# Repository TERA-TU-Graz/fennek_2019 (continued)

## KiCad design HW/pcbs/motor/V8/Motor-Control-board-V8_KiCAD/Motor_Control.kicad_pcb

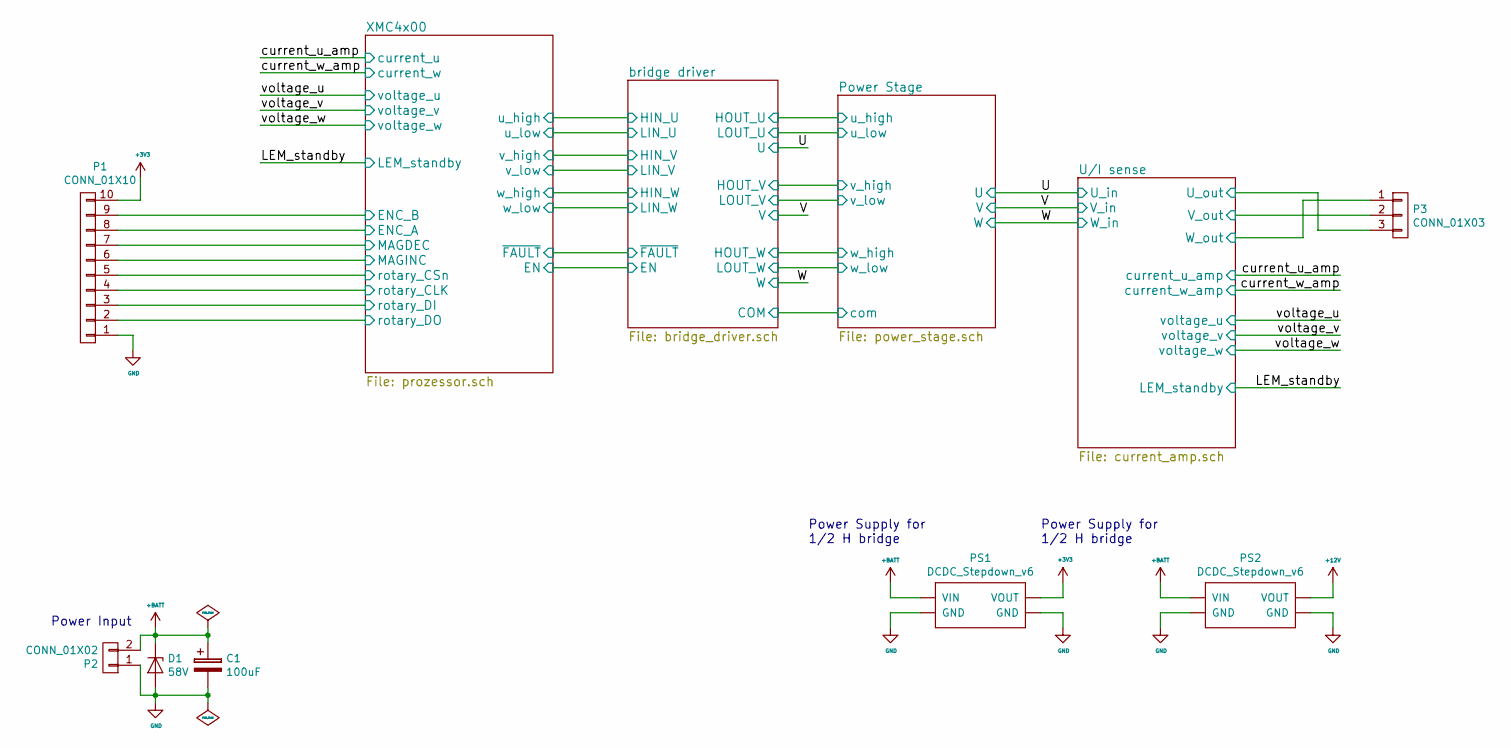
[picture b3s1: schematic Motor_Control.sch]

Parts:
C1: 100uF; ElkoC-12.5x20mm-horizontal
D1: 58V; DO-214AA
P1: CONN_01X10; Molex_PicoBlade_53261-1071_10x1.25mm_Angled
P2: CONN_01X02; MSTBV_2.5_2-GF-5.08mm
P3: CONN_01X03; PhoenixContact_MSTBA-G_03x5.08mm_Angled
PS1, PS2: DCDC_Stepdown_v6

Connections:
+3V3: P1.10, PS1.2 (VOUT); also elsewhere on the board
+12V: PS2.2 (VOUT); also elsewhere on the board
+BATT: C1.1, D1.1 (K), P2.2, PS1.1 (VIN), PS2.1 (VIN); also elsewhere on the board
/U/I sense/U_out: P3.3; also elsewhere on the board
/U/I sense/W_out: P3.1; also elsewhere on the board
/V: P3.2; also elsewhere on the board
/XMC4x00/ENC_A: P1.8; also elsewhere on the board
/XMC4x00/ENC_B: P1.9; also elsewhere on the board
/XMC4x00/MAGDEC: P1.7; also elsewhere on the board
/XMC4x00/MAGINC: P1.6; also elsewhere on the board
/XMC4x00/rotary_CLK: P1.4; also elsewhere on the board
/XMC4x00/rotary_CSn: P1.5; also elsewhere on the board
/XMC4x00/rotary_DI: P1.3; also elsewhere on the board
/XMC4x00/rotary_DO: P1.2; also elsewhere on the board
GND: C1.2, D1.2 (A), P1.1, P2.1, PS1.3 (GND), PS1.4 (GND), PS2.3 (GND), PS2.4 (GND); also elsewhere on the board

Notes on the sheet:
Power Supply for 1/2 H bridge
Power Input

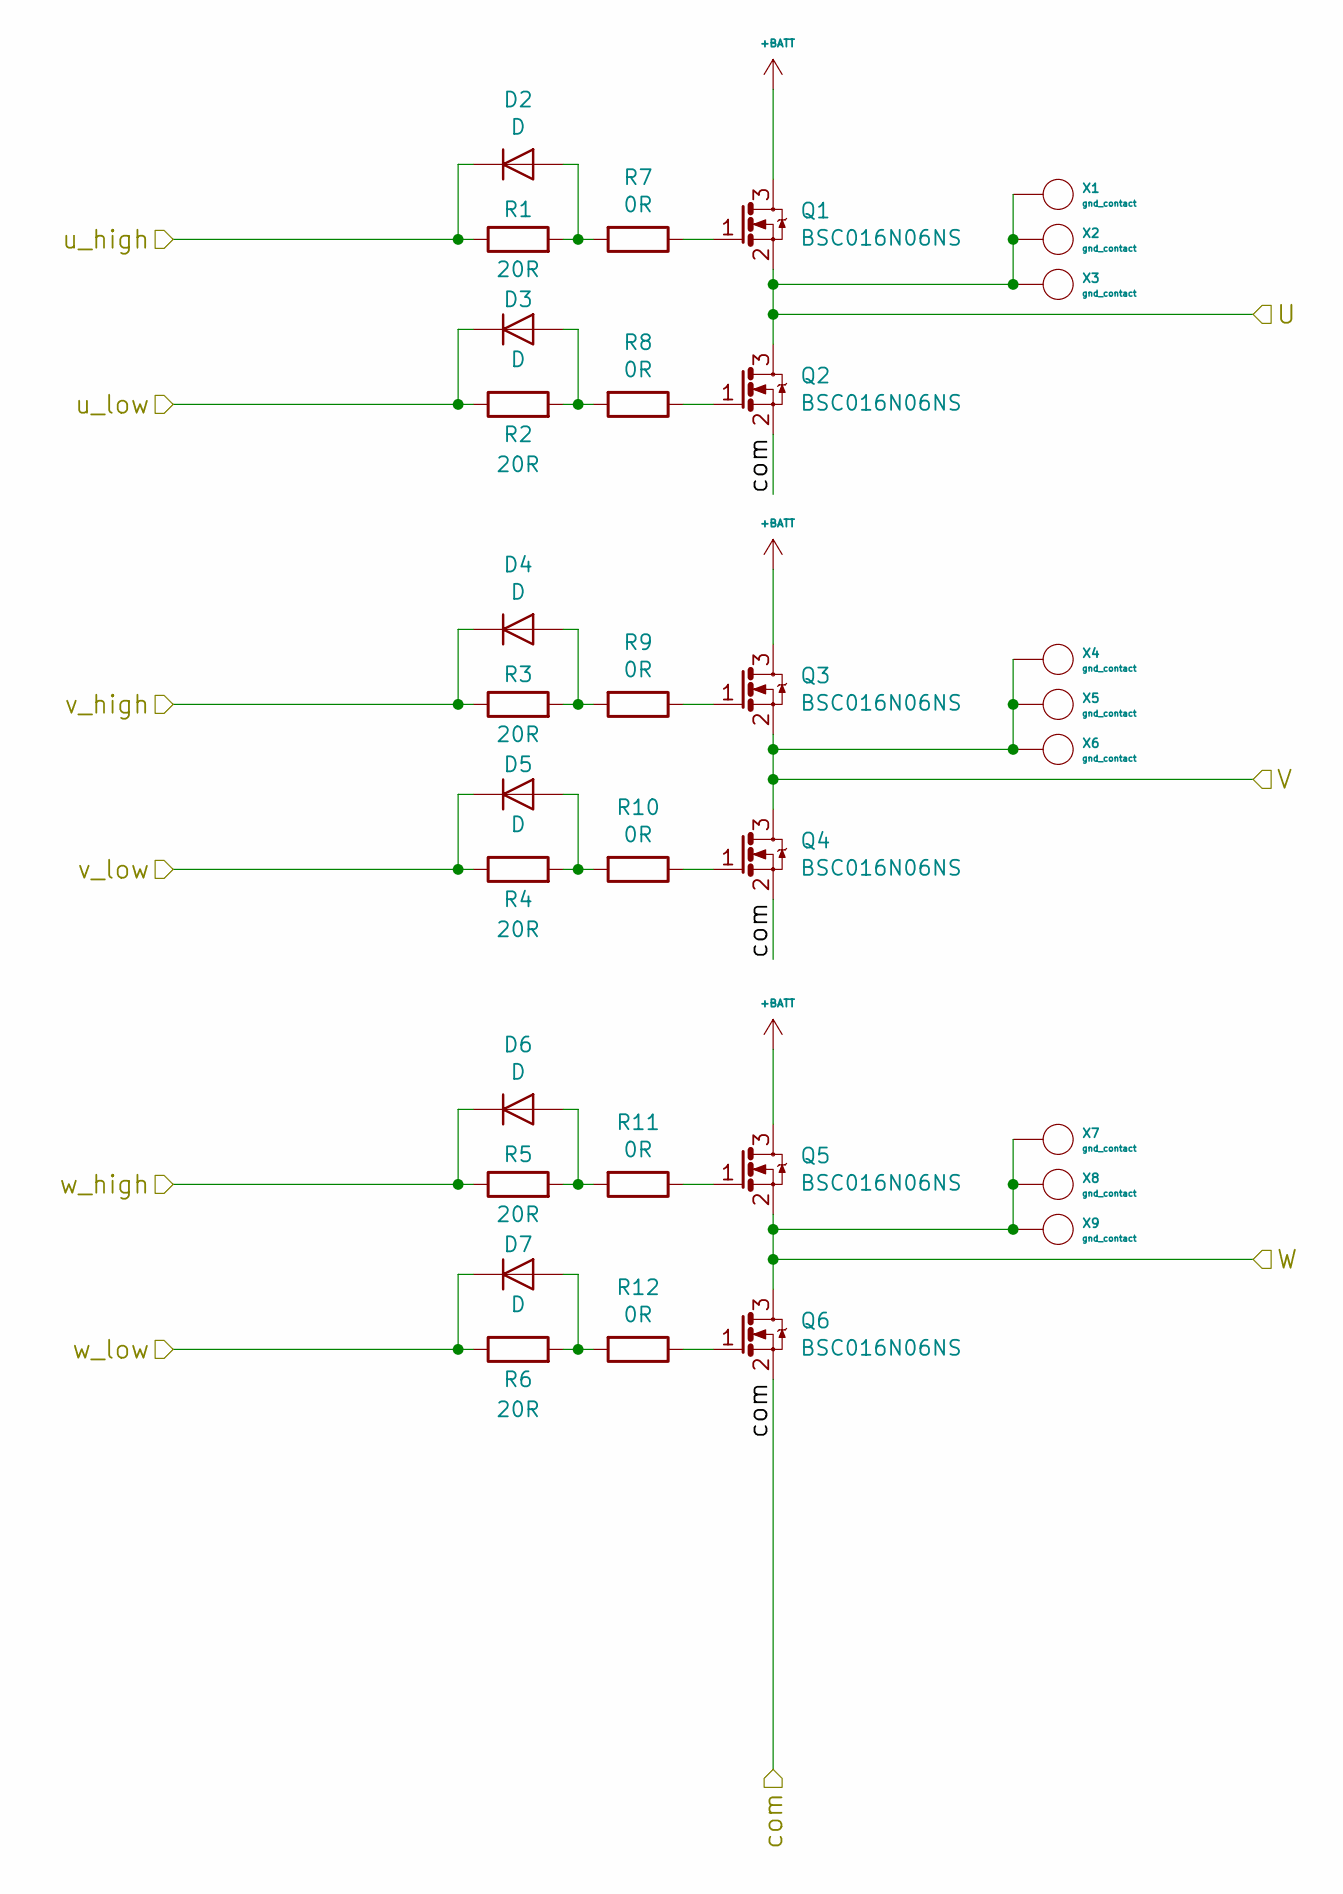
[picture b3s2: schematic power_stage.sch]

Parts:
D2, D3, D4, D5, D6, D7: D; SOD-323
Q1, Q2, Q3, Q4, Q5, Q6: BSC016N06NS; INF-PG-TDSON-8
R1, R2, R3, R4, R5, R6: 20R; R_0603in
R7, R8, R9, R10, R11, R12: 0R; R_0603in
X1, X2, X3, X4, X5, X6, X7, X8, X9: gnd_contact; via_0.4mm

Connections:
+BATT: Q1.3 (D), Q3.3 (D), Q5.3 (D); also elsewhere on the board
/U: Q1.2 (S), Q2.3 (D), X1.1, X2.1, X3.1; also elsewhere on the board
/V: Q3.2 (S), Q4.3 (D), X4.1, X5.1, X6.1; also elsewhere on the board
/W: Q5.2 (S), Q6.3 (D), X7.1, X8.1, X9.1; also elsewhere on the board
/bridge driver/COM: Q2.2 (S), Q4.2 (S), Q6.2 (S); also elsewhere on the board
/bridge driver/HOUT_U: D2.1 (K), R1.1; also elsewhere on the board
/bridge driver/HOUT_V: D4.1 (K), R3.1; also elsewhere on the board
/bridge driver/HOUT_W: D6.1 (K), R5.1; also elsewhere on the board
/bridge driver/LOUT_U: D3.1 (K), R2.1; also elsewhere on the board
/bridge driver/LOUT_V: D5.1 (K), R4.1; also elsewhere on the board
/bridge driver/LOUT_W: D7.1 (K), R6.1; also elsewhere on the board
unnamed: D2.2 (A), R1.2, R7.2
unnamed: D3.2 (A), R2.2, R8.2
unnamed: D4.2 (A), R3.2, R9.2
unnamed: D5.2 (A), R4.2, R10.2
unnamed: D6.2 (A), R5.2, R11.2
unnamed: D7.2 (A), R6.2, R12.2
unnamed: Q1.1 (G), R7.1
unnamed: Q2.1 (G), R8.1
unnamed: Q3.1 (G), R9.1
unnamed: Q4.1 (G), R10.1
unnamed: Q5.1 (G), R11.1
unnamed: Q6.1 (G), R12.1

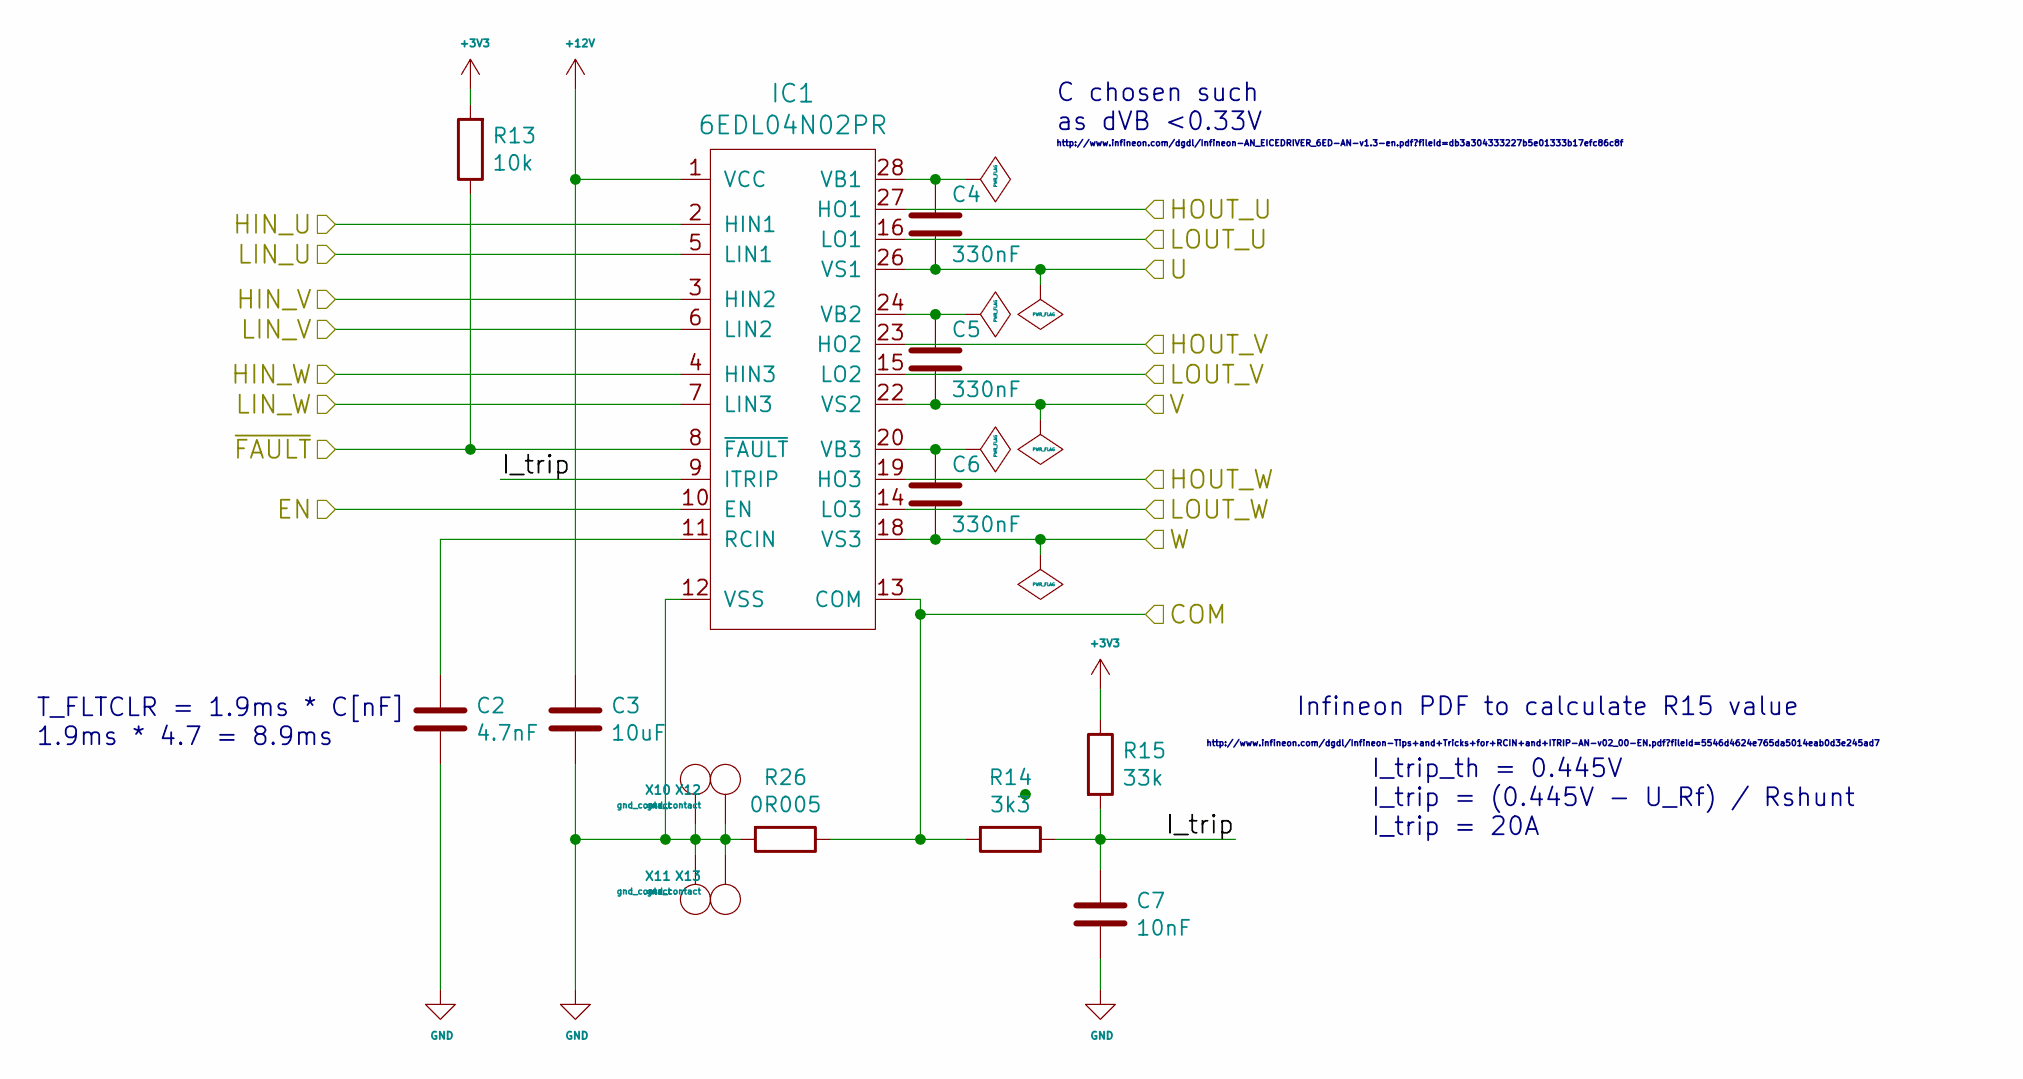
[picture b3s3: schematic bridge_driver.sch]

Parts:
C2: 4.7nF; C_0603in
C3: 10uF; C_0603in
C4, C5, C6: 330nF; C_0603in
C7: 10nF; C_0603in
IC1: 6EDL04N02PR
R13: 10k; R_0603in
R14: 3k3; R_0603in
R15: 33k; R_0603in
R26: 0R005; R_2512in
X10, X11, X12, X13: gnd_contact; via_0.4mm

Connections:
+3V3: R13.2, R15.1; also elsewhere on the board
+12V: C3.1, IC1.1 (VCC); also elsewhere on the board
/U: C4.2, IC1.26 (VS1); also elsewhere on the board
/V: C5.2, IC1.22 (VS2); also elsewhere on the board
/W: C6.2, IC1.18 (VS3); also elsewhere on the board
/XMC4x00/EN: IC1.10 (EN); also elsewhere on the board
/XMC4x00/~FAULT: IC1.8 (~FAULT), R13.1; also elsewhere on the board
/bridge driver/COM: IC1.13 (COM), R14.2, R26.1; also elsewhere on the board
/bridge driver/HIN_U: IC1.2 (HIN1); also elsewhere on the board
/bridge driver/HIN_V: IC1.3 (HIN2); also elsewhere on the board
/bridge driver/HIN_W: IC1.4 (HIN3); also elsewhere on the board
/bridge driver/HOUT_U: IC1.27 (HO1); also elsewhere on the board
/bridge driver/HOUT_V: IC1.23 (HO2); also elsewhere on the board
/bridge driver/HOUT_W: IC1.19 (HO3); also elsewhere on the board
/bridge driver/I_trip: C7.1, IC1.9 (ITRIP), R14.1, R15.2
/bridge driver/LIN_U: IC1.5 (LIN1); also elsewhere on the board
/bridge driver/LIN_V: IC1.6 (LIN2); also elsewhere on the board
/bridge driver/LIN_W: IC1.7 (LIN3); also elsewhere on the board
/bridge driver/LOUT_U: IC1.16 (LO1); also elsewhere on the board
/bridge driver/LOUT_V: IC1.15 (LO2); also elsewhere on the board
/bridge driver/LOUT_W: IC1.14 (LO3); also elsewhere on the board
GND: C2.2, C3.2, C7.2, IC1.12 (VSS), R26.2, X10.1, X11.1, X12.1, X13.1; also elsewhere on the board
unnamed: C2.1, IC1.11 (RCIN)
unnamed: C4.1, IC1.28 (VB1)
unnamed: C5.1, IC1.24 (VB2)
unnamed: C6.1, IC1.20 (VB3)

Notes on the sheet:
http://www.infineon.com/dgdl/Infineon-Tips+and+Tricks+for+RCIN+and+ITRIP-AN-v02_00-EN.pdf?fileId=5546d4624e765da5014eab0d3e245ad7
Infineon PDF to calculate R15 value
T_FLTCLR = 1.9ms * C[nF] 1.9ms * 4.7 = 8.9ms
C chosen such as dVB <0.33V
I_trip_th = 0.445V I_trip = (0.445V - U_Rf) / Rshunt I_trip = 20A
http://www.infineon.com/dgdl/Infineon-AN_EICEDRIVER_6ED-AN-v1.3-en.pdf?fileId=db3a304333227b5e01333b17efc86c8f

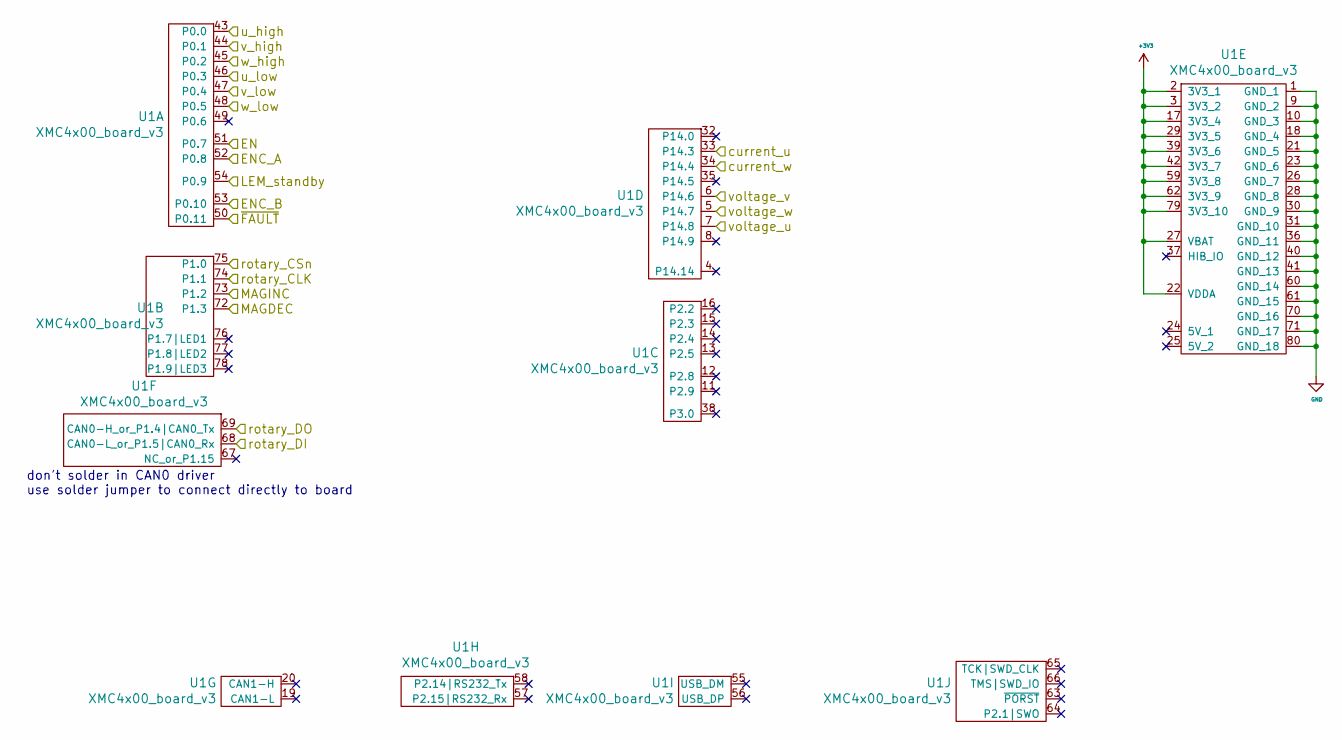
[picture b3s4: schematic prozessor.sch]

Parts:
U1: XMC4x00_board_v3; XMC4x00-board_v3-0

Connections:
+3V3: U1.2 (3V3_1), U1.3 (3V3_2), U1.17 (3V3_4), U1.22 (VDDA), U1.27 (VBAT), U1.29 (3V3_5), U1.39 (3V3_6), U1.42 (3V3_7), U1.59 (3V3_8), U1.62 (3V3_9), U1.79 (3V3_10); also elsewhere on the board
/LEM_standby: U1.54 (P0.9); also elsewhere on the board
/XMC4x00/EN: U1.51 (P0.7); also elsewhere on the board
/XMC4x00/ENC_A: U1.52 (P0.8); also elsewhere on the board
/XMC4x00/ENC_B: U1.53 (P0.10); also elsewhere on the board
/XMC4x00/MAGDEC: U1.72 (P1.3); also elsewhere on the board
/XMC4x00/MAGINC: U1.73 (P1.2); also elsewhere on the board
/XMC4x00/rotary_CLK: U1.74 (P1.1); also elsewhere on the board
/XMC4x00/rotary_CSn: U1.75 (P1.0); also elsewhere on the board
/XMC4x00/rotary_DI: U1.68 (CAN0-L_or_P1.5|CAN0_Rx); also elsewhere on the board
/XMC4x00/rotary_DO: U1.69 (CAN0-H_or_P1.4|CAN0_Tx); also elsewhere on the board
/XMC4x00/~FAULT: U1.50 (P0.11); also elsewhere on the board
/bridge driver/HIN_U: U1.43 (P0.0); also elsewhere on the board
/bridge driver/HIN_V: U1.44 (P0.1); also elsewhere on the board
/bridge driver/HIN_W: U1.45 (P0.2); also elsewhere on the board
/bridge driver/LIN_U: U1.46 (P0.3); also elsewhere on the board
/bridge driver/LIN_V: U1.47 (P0.4); also elsewhere on the board
/bridge driver/LIN_W: U1.48 (P0.5); also elsewhere on the board
/current_u_amp: U1.33 (P14.3); also elsewhere on the board
/current_w_amp: U1.34 (P14.4); also elsewhere on the board
/voltage_u: U1.7 (P14.8); also elsewhere on the board
/voltage_v: U1.6 (P14.6); also elsewhere on the board
/voltage_w: U1.5 (P14.7); also elsewhere on the board
GND: U1.1 (GND_1), U1.9 (GND_2), U1.10 (GND_3), U1.18 (GND_4), U1.21 (GND_5), U1.23 (GND_6), U1.26 (GND_7), U1.28 (GND_8), U1.30 (GND_9), U1.31 (GND_10), U1.36 (GND_11), U1.40 (GND_12), U1.41 (GND_13), U1.60 (GND_14), U1.61 (GND_15), U1.70 (GND_16), U1.71 (GND_17), U1.80 (GND_18); also elsewhere on the board

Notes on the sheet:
don't solder in CAN0 driver use solder jumper to connect directly to board

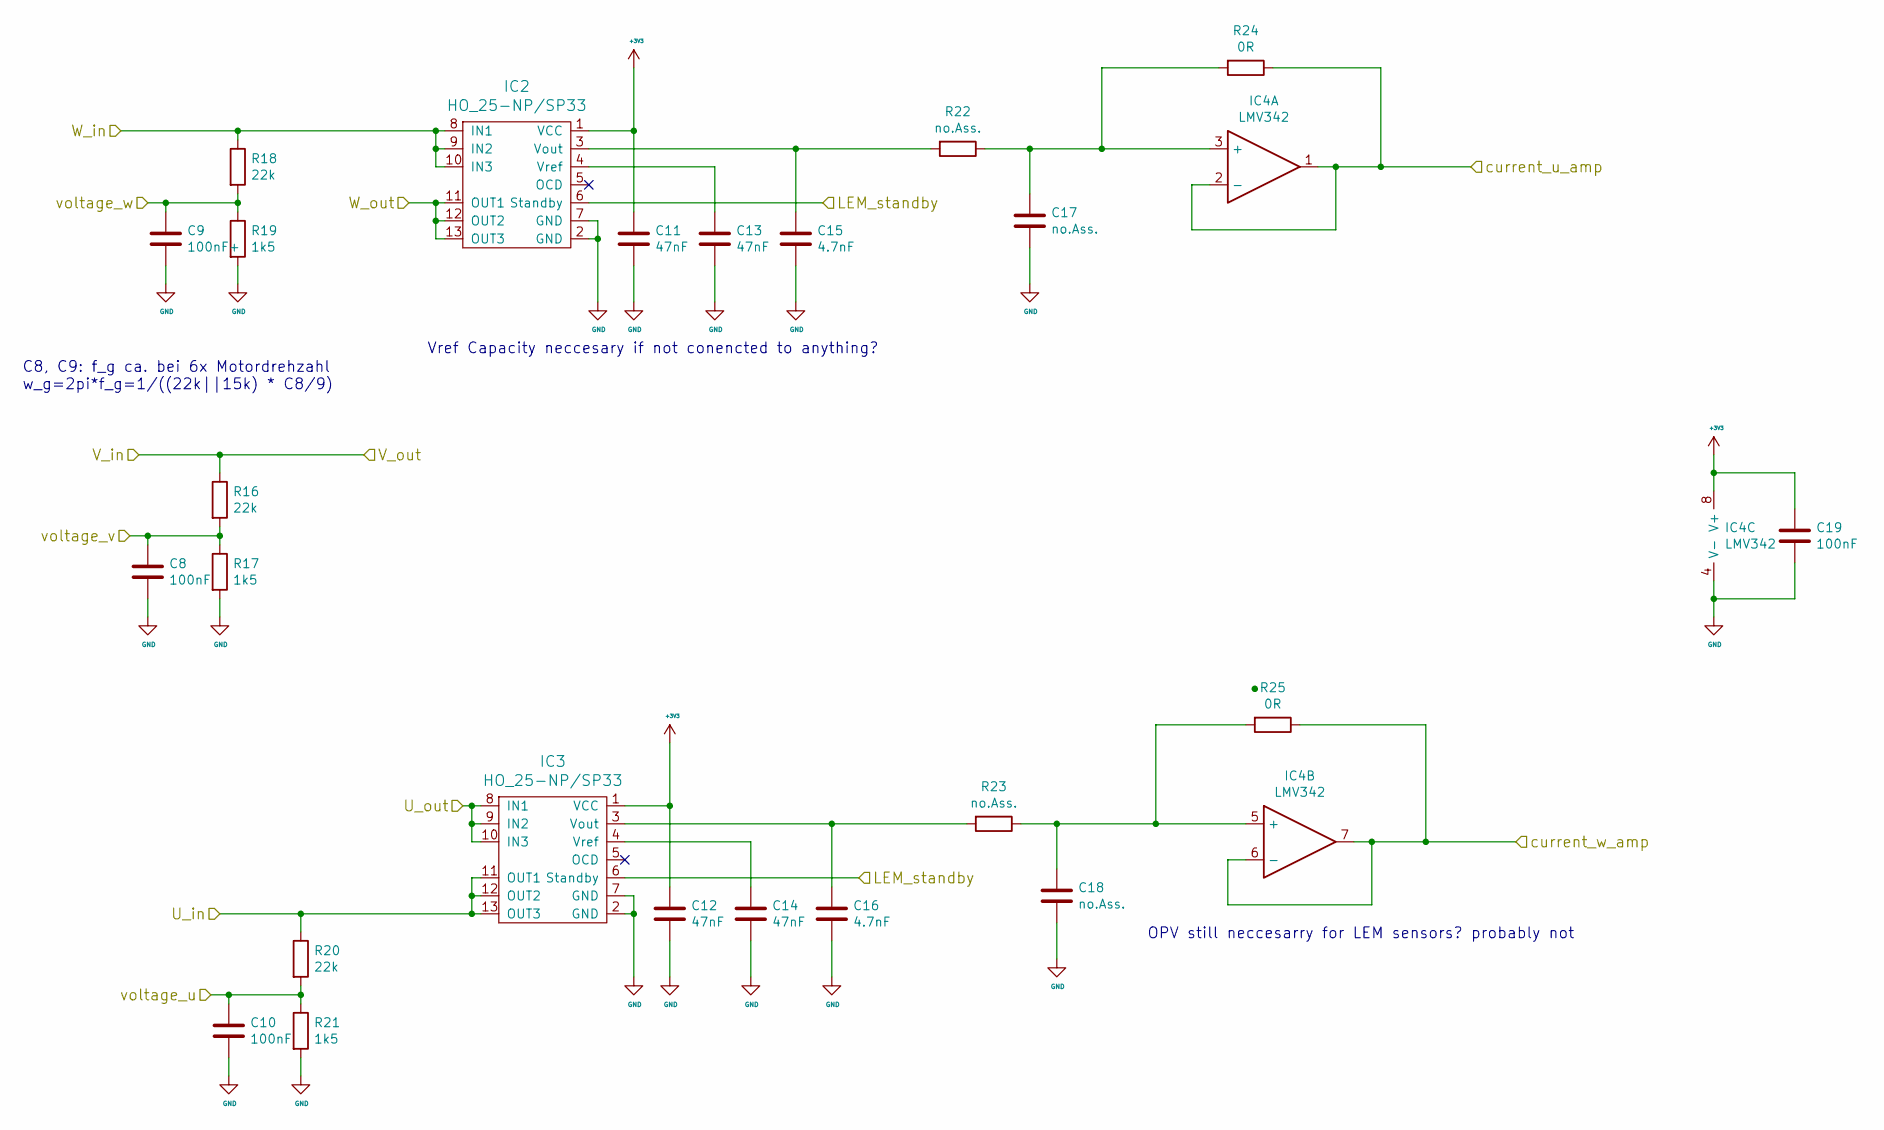
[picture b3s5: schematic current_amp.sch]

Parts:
C8, C10, C19: 100nF; C_0603in
C9: 100nF+; C_0603in
C11, C12, C13, C14: 47nF; C_0603in
C15, C16: 4.7nF; C_0603in
C17, C18: no.Ass.; C_0603in
IC2, IC3: HO_25-NP/SP33; HO_25-NP_SP33
IC4: LMV342
R16, R18, R20: 22k; R_0603in
R17, R19, R21: 1k5; R_0603in
R22, R23: no.Ass.; R_0603in
R24, R25: 0R; R_0603in

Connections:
+3V3: C11.1, C12.1, C19.1, IC2.1 (VCC), IC3.1 (VCC), IC4.8 (V+); also elsewhere on the board
/LEM_standby: IC2.6 (Standby), IC3.6 (Standby); also elsewhere on the board
/U: IC3.11 (OUT1), IC3.12 (OUT2), IC3.13 (OUT3), R20.1; also elsewhere on the board
/U/I sense/U_out: IC3.8 (IN1), IC3.9 (IN2), IC3.10 (IN3); also elsewhere on the board
/U/I sense/W_out: IC2.11 (OUT1), IC2.12 (OUT2), IC2.13 (OUT3); also elsewhere on the board
/V: R16.1; also elsewhere on the board
/W: IC2.8 (IN1), IC2.9 (IN2), IC2.10 (IN3), R18.1; also elsewhere on the board
/current_u_amp: IC4.1, IC4.2 (-), R24.1; also elsewhere on the board
/current_w_amp: IC4.6 (-), IC4.7, R25.1; also elsewhere on the board
/voltage_u: C10.1, R20.2, R21.1; also elsewhere on the board
/voltage_v: C8.1, R16.2, R17.1; also elsewhere on the board
/voltage_w: C9.1, R18.2, R19.1; also elsewhere on the board
GND: C8.2, C9.2, C10.2, C11.2, C12.2, C13.2, C14.2, C15.2, C16.2, C17.2, C18.2, C19.2, IC2.2 (GND), IC2.7 (GND), IC3.2 (GND), IC3.7 (GND), IC4.4 (V-), R17.2, R19.2, R21.2; also elsewhere on the board
unnamed: C13.1, IC2.4 (Vref)
unnamed: C14.1, IC3.4 (Vref)
unnamed: C15.1, IC2.3 (Vout), R22.2
unnamed: C16.1, IC3.3 (Vout), R23.2
unnamed: C17.1, IC4.3 (+), R22.1, R24.2
unnamed: C18.1, IC4.5 (+), R23.1, R25.2

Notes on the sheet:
OPV still neccesarry for LEM sensors? probably not
Vref Capacity neccesary if not conencted to anything?
C8, C9: f_g ca. bei 6x Motordrehzahl w_g=2pi*f_g=1/((22k||15k) * C8/9)

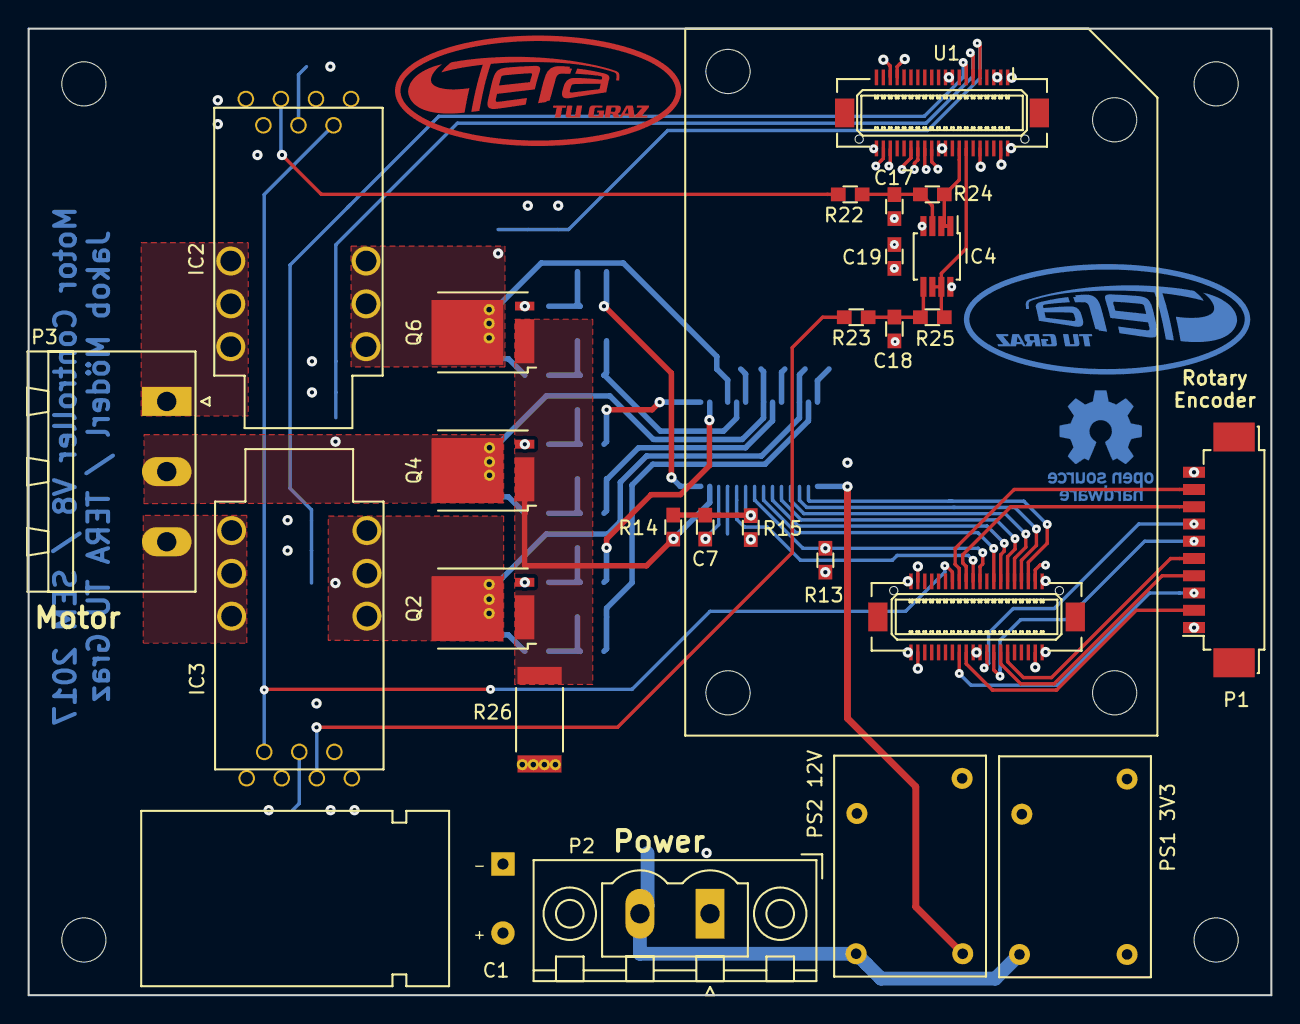
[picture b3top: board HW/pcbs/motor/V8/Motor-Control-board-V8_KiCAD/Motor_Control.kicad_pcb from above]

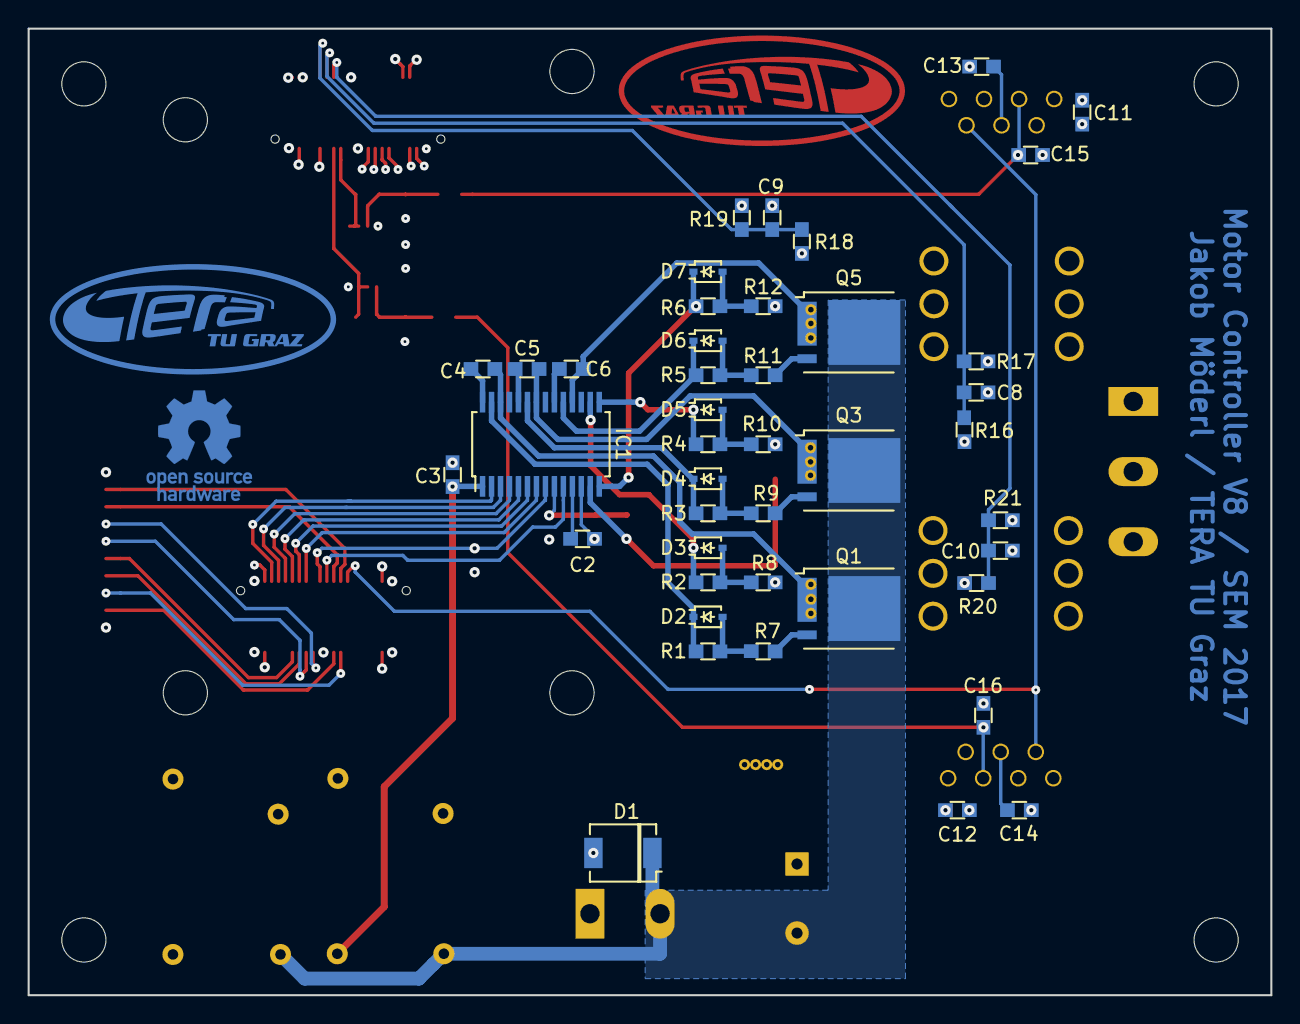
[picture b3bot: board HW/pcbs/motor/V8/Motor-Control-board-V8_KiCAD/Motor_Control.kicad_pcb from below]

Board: 4 copper layers, 90.0 x 70.0 mm, 83 parts (51 on the bottom side), 61 nets.

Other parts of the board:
svg2mod, svg2mod#2: G***; TERA_Logo_Cu_7.5x19mm

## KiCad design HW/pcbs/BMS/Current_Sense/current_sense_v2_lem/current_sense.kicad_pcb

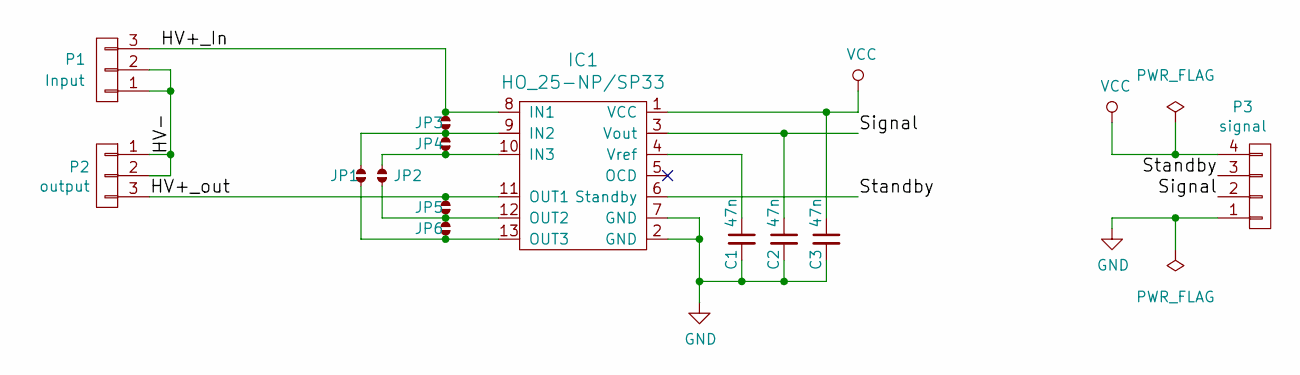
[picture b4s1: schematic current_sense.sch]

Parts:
C1, C2, C3: 47n; C_0603in
IC1: HO_25-NP/SP33; HO_25-NP_SP33
JP1, JP2: 1/3 Range; SOLDERJUMPER_2
JP3, JP4, JP5, JP6: Full_Range; SOLDERJUMPER_2
P1: Input; PhoenixContact_MSTBVA-G_03x5.08mm_Vertical
P2: output; PhoenixContact_MSTBA-G_03x5.08mm_Angled
P3: signal; Molex_PicoBlade_53261-0471_04x1.25mm_Angled

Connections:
/HV+_In: IC1.8 (IN1), JP3.1 (A), P1.3
/HV+_out: IC1.11 (OUT1), JP5.1 (A), P2.3
/HV-: P1.1, P1.2, P2.1, P2.2
/Signal: C2.1, IC1.3 (Vout), P3.2
/Standby: IC1.6 (Standby), P3.3
GND: C1.2, C2.2, C3.2, IC1.2 (GND), IC1.7 (GND), P3.1
unnamed: C1.1, IC1.4 (Vref)
unnamed: IC1.9 (IN2), JP1.1 (A), JP3.2 (B), JP4.1 (A)
unnamed: IC1.10 (IN3), JP2.1 (A), JP4.2 (B)
unnamed: IC1.12 (OUT2), JP2.2 (B), JP5.2 (B), JP6.1 (A)
unnamed: IC1.13 (OUT3), JP1.2 (B), JP6.2 (B)
VCC: C3.1, IC1.1 (VCC), P3.4

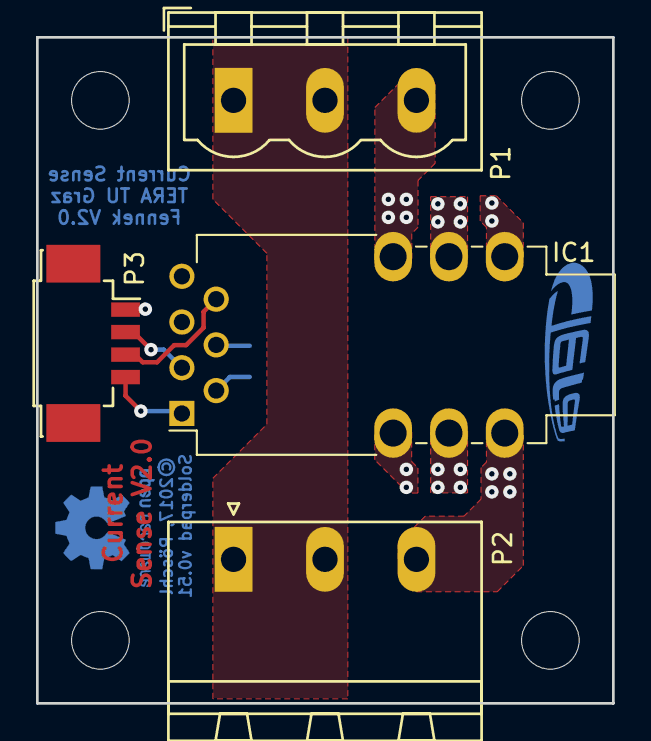
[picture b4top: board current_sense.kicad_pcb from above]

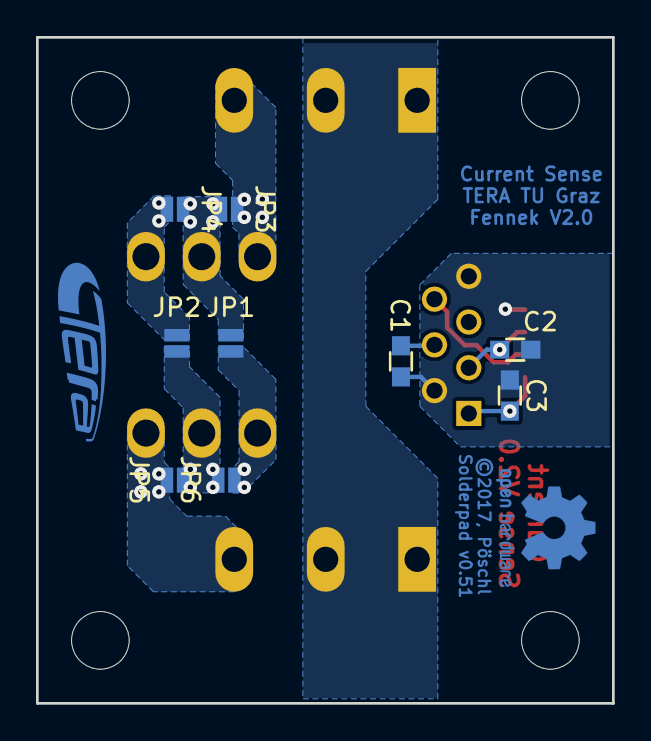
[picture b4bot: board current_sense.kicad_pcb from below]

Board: 2 copper layers, 32.0 x 37.0 mm, 14 parts (10 on the bottom side), 12 nets.

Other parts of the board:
svg2mod: G***; TERA_TextOnly_Cu_2.5x9.5mm
